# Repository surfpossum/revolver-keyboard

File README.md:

# CREDITS
- Christian Selig's excellent video provided a fantastic step-by-step starting point
	https://www.youtube.com/watch?v=7UXsD7nSfDY
- ergogen is some incredible software, and the blog post below was a fun read
	https://ergogen.ceoloide.com/
	https://zealot.hu/absolem/
- kicad is similarly incredible
	https://www.kicad.org/
- flatfootfox's ergogent tutorial was very helpful
	https://flatfootfox.com/ergogen-introduction/
- Ben Vallack had a ton of useful stuff
	https://www.youtube.com/watch?v=M_VuXVErD6E
- cradio was used for looking up direct wired keys
	https://github.com/zmkfirmware/zmk/blob/main/app/boards/shields/cradio/
- asetniop served as the inspiration for making this nonsense
	https://asetniop.com/

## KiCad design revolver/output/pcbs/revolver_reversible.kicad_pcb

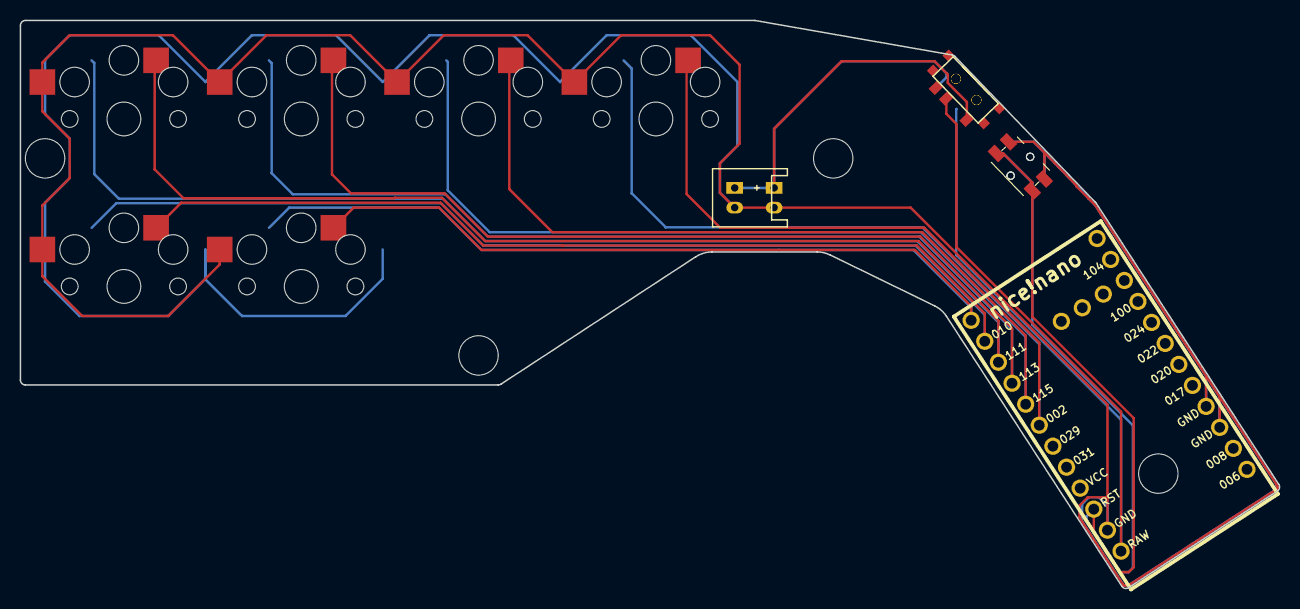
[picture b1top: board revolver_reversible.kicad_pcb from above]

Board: 2 copper layers, 127.8 x 57.7 mm, 13 parts (0 on the bottom side), 10 nets.

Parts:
B1, B2: Panasonic_EVQPUL_EVQPUC
JST1, JST2: JST_PH_S2B-PH-K_02x2.00mm_Angled
MCU1: nice_nano
S7, S8, S9, S10, S11, S12: PG1350
T1, T2: SPDT_C128955

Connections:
GND: B1.1, B2.1, JST1.2, JST2.2, MCU1.3, MCU1.4, MCU1.23, S7.2, S8.2, S9.2, S10.2, S11.2, S12.2
P002: MCU1.18, S12.1
P009: MCU1.13, S10.1
P010: MCU1.14, S8.1
P111: MCU1.15, S7.1
P113: MCU1.16, S9.1
P115: MCU1.17, S11.1
RAW: MCU1.24, T1.2, T2.2
RST: B1.2, B2.2, MCU1.22
pos: JST1.1, JST2.1, T1.1, T2.1

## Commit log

2025-02-22 Initial User Config.
2025-02-22 renaming config files
2025-02-22 created config files
2025-02-23 assigned some column pins?
2025-02-24 added footprints from caldera; finished up ergogen yaml; routed stuff in kicad
2025-02-24 updated dtsi and overlays based on cradio, a direct wired layout
2025-02-25 starting to mess with keymap
2025-02-25 starting to add combos
2025-02-25 messing around with keymap and also temporarily storing my np++ theme
2025-02-26 updated build.yaml
2025-02-26 adding left and right .conf files
2025-02-26 moving .keymap up into config
2025-02-26 restructuring to not have zmk-config-revolver be top level
2025-02-26 still trying to restructure to get things to build
2025-02-26 trying to re-trigger workflow
2025-02-26 moving workflow folder back up
2025-02-26 maybe i deleted a # from the build.yaml?
2025-02-26 still trying to structure things to build
2025-02-26 fixing lowercase keybindings in keymap
2025-02-26 fixing erroneous / in keymap
